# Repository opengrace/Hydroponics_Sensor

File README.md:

Hydroponics_Sensor
==================

**Warning** _currently untested, may contain errors._

An ebb and flow hydroponics or CHPIS aquaponics sensor breakout and controller that uses a NRF24L01 module for communication to other nodes or a central server.

|![image1]|![image2]|
|---|---|
|Board partially populated.||

[image1]: pic-1.JPG "Arduino nano and 10 pin NRF24L01 module"
[image2]: pic-2.JPG "Arduino nano and 10 pin NRF24L01 module"

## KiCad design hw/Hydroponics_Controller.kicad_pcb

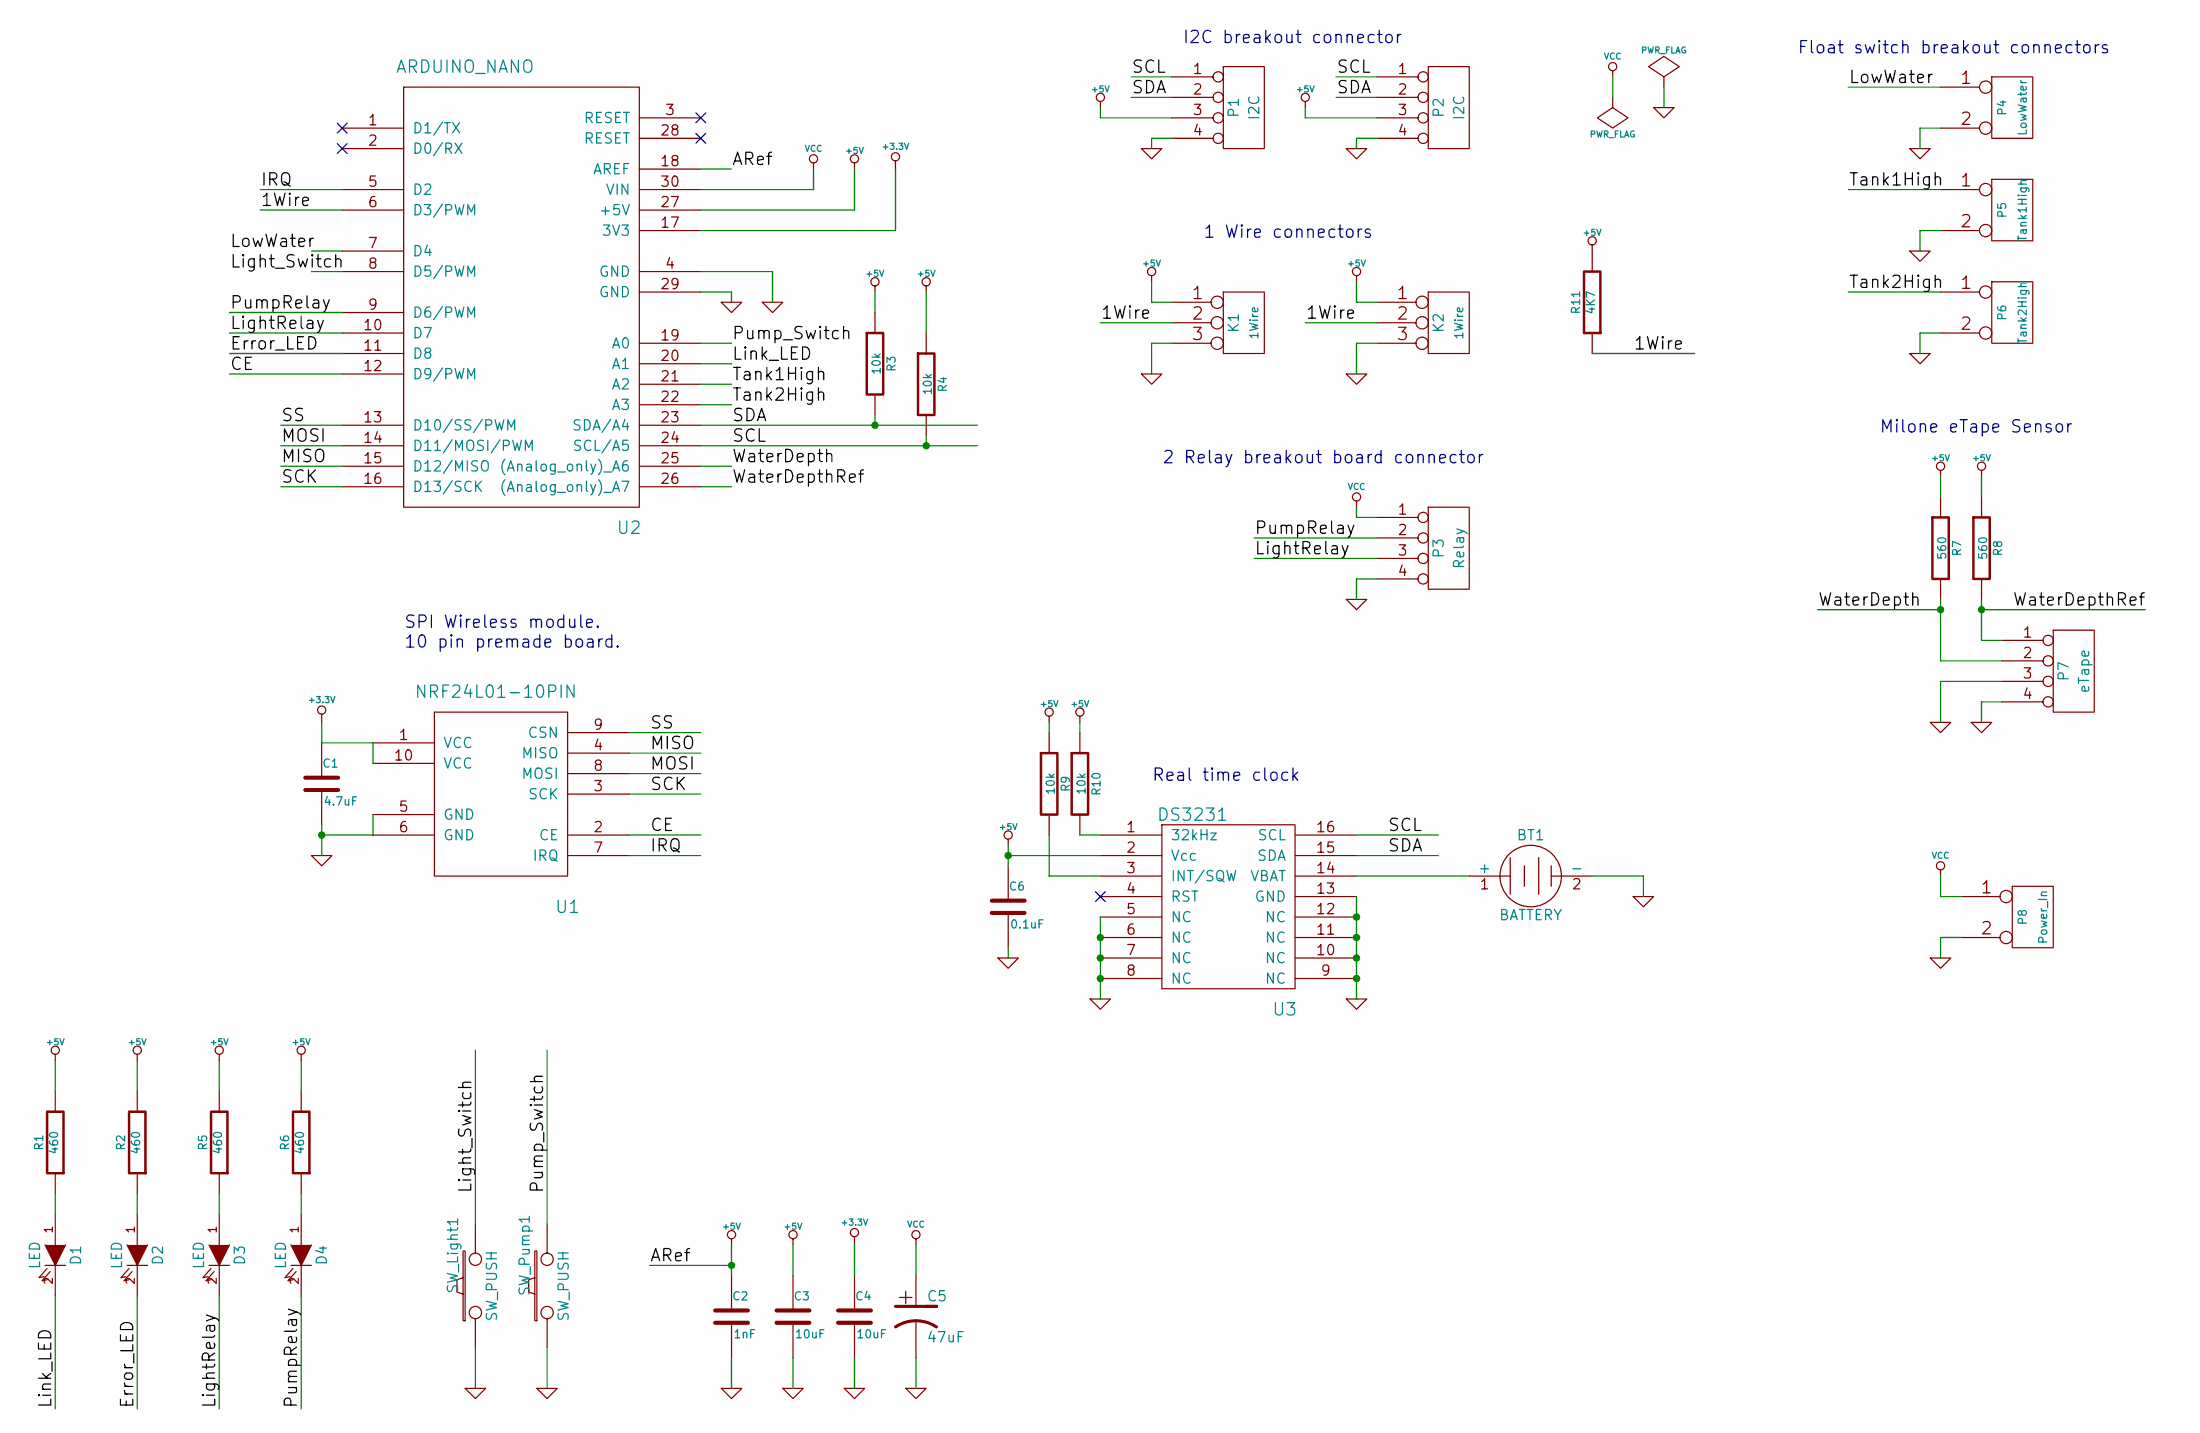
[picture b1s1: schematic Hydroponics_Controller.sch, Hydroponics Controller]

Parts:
BT1: BATTERY
C1: 4.7uF
C2: 1nF
C3, C4: 10uF
C5: 47uF
C6: 0.1uF
D1, D2, D3, D4: LED
K1, K2: 1Wire
P1, P2: I2C
P3: Relay
P4: LowWater
P5: Tank1High
P6: Tank2High
P7: eTape
P8: Power_In
R1, R2, R5, R6: 460
R3, R4, R9, R10: 10k
R7, R8: 560
R11: 4K7
SW_Light1: SW_PUSH
SW_Pump1: SW_PUSH
U1: NRF24L01-10PIN
U2: ARDUINO_NANO
U3: DS3231

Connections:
+3.3V: C1.1, C4.1, U1.1 (VCC), U1.10 (VCC), U2.17 (3V3)
+5V: C2.1, C3.1, C6.1, K1.1, K2.1, P1.3, P2.3, R1.2, R2.2, R3.1, R4.1, R5.2, R6.2, R7.1, R8.1, R9.1, R10.1, R11.2, U2.18 (AREF), U2.27 (+5V), U3.2 (Vcc)
/1Wire: K1.2 (PM), K2.2 (PM), R11.1, U2.6 (D3/PWM)
/CE: U1.2 (CE), U2.12 (D9/PWM)
/Error_LED: D2.2 (K), U2.11 (D8)
/IRQ: U1.7 (IRQ), U2.5 (D2)
/LightRelay: D3.2 (K), P3.3, U2.10 (D7)
/Light_Switch: SW_Light1.2
/Link_LED: D1.2 (K), U2.20 (A1)
/LowWater: P4.1
/MISO: U1.4 (MISO), U2.15 (D12/MISO)
/MOSI: U1.8 (MOSI), U2.14 (D11/MOSI/PWM)
/PumpRelay: D4.2 (K), P3.2, U2.9 (D6/PWM)
/Pump_Switch: SW_Pump1.2, U2.19 (A0)
/SCK: U1.3 (SCK), U2.16 (D13/SCK)
/SCL: P1.1, P2.1, R4.2, U2.24 (SCL/A5), U3.16 (SCL)
/SDA: P1.2, P2.2, R3.2, U2.23 (SDA/A4), U3.15 (SDA)
/SS: U1.9 (CSN), U2.13 (D10/SS/PWM)
/Tank1High: P5.1, U2.21 (A2)
/Tank2High: P6.1, U2.22 (A3)
/WaterDepth: P7.2, R7.2, U2.25 ((Analog_only)_A6)
/WaterDepthRef: P7.1, R8.2, U2.26 ((Analog_only)_A7)
GND: BT1.2 (-), C1.2, C2.2, C3.2, C4.2, C5.2, C6.2, K1.3, K2.3, P1.4, P2.4, P3.4, P4.2 (PM), P5.2 (PM), P6.2 (PM), P7.3, P7.4, P8.2 (PM), SW_Light1.1, SW_Pump1.1, U1.5 (GND), U1.6 (GND), U2.4 (GND), U2.29 (GND), U3.5 (NC), U3.6 (NC), U3.7 (NC), U3.8 (NC), U3.9 (NC), U3.10 (NC), U3.11 (NC), U3.12 (NC), U3.13 (GND)
unnamed: BT1.1 (+), U3.14 (VBAT)
unnamed: D1.1 (A), R1.1
unnamed: D2.1 (A), R2.1
unnamed: D3.1 (A), R5.1
unnamed: D4.1 (A), R6.1
unnamed: R9.2, U3.3 (INT/SQW)
unnamed: R10.2, U3.1 (32kHz)
VCC: C5.1, P3.1, P8.1, U2.30 (VIN)

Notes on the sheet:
SPI Wireless module. 10 pin premade board.
Float switch breakout connectors
Milone eTape Sensor
I2C breakout connector
1 Wire connectors
2 Relay breakout board connector
Real time clock

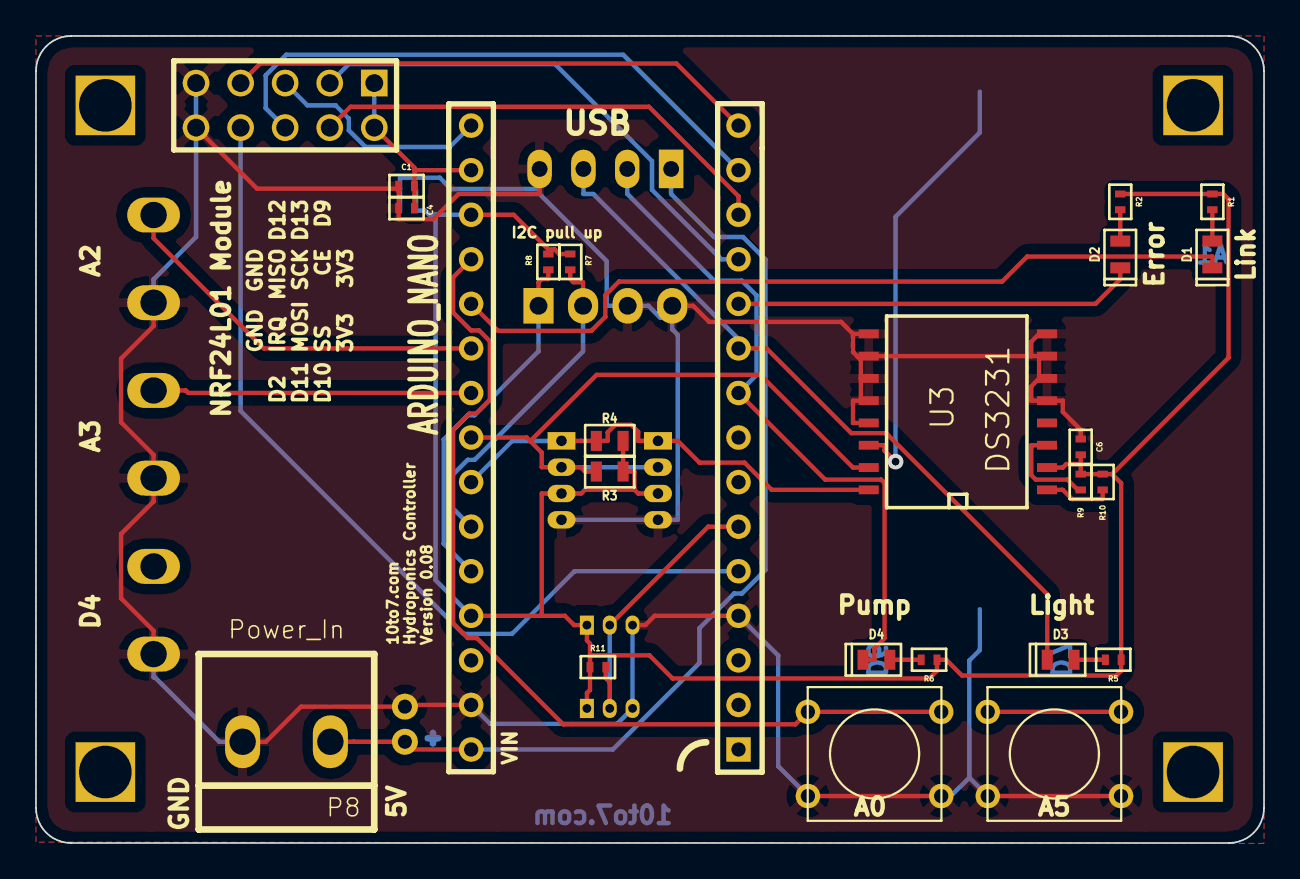
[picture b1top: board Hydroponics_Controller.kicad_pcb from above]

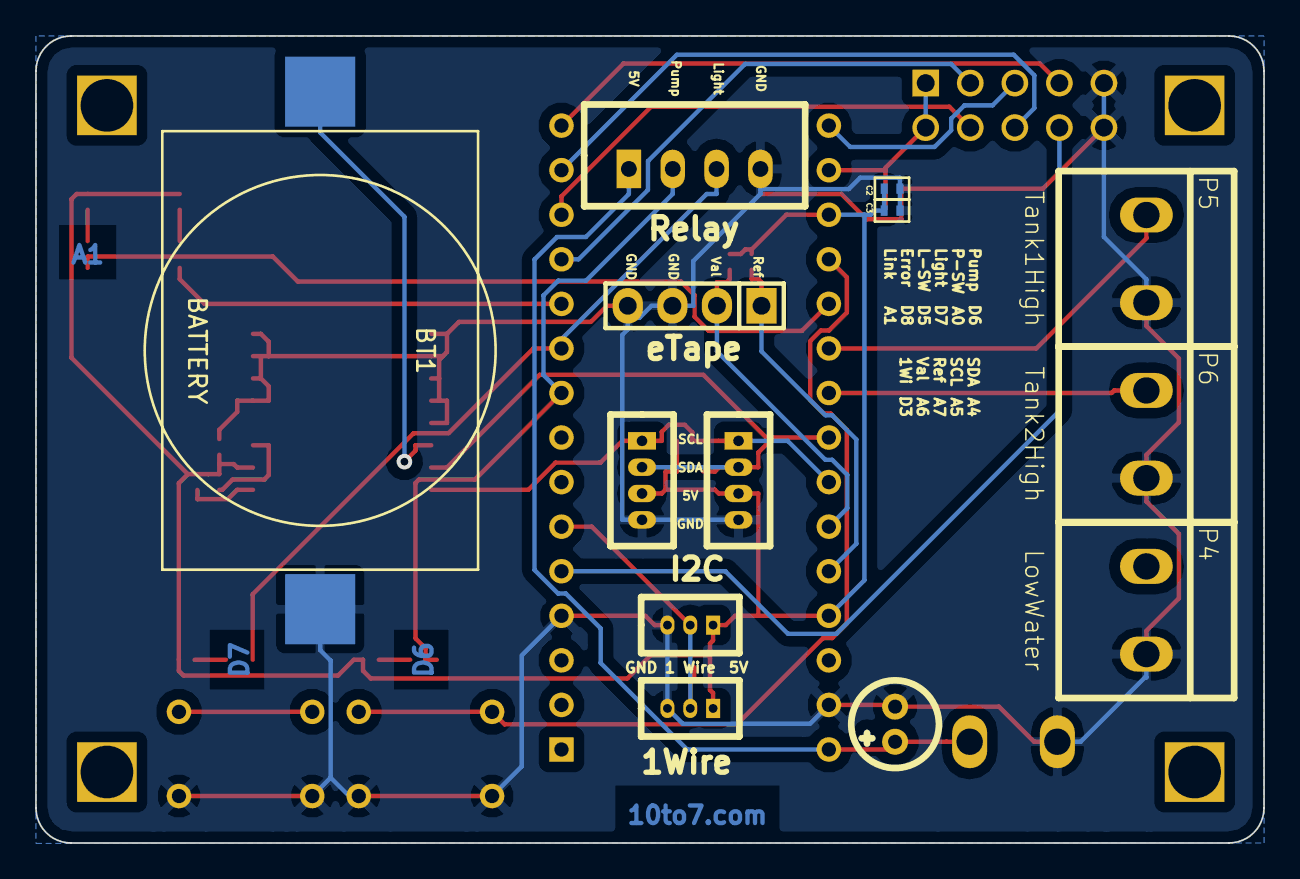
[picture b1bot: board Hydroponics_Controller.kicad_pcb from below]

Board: 2 copper layers, 70.0 x 46.0 mm, 41 parts (13 on the bottom side), 29 nets.

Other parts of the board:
3mmHole_1, 3mmHole_2, 3mmHole_3, 3mmHole_4: VAL**; 3mmHole

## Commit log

2014-05-18 Recreated and moved to new repository
2014-05-31 removed some un-needed components, updated faulty modules and reduced board size.
2014-05-31 and the gerber files
2014-06-01 Fixed text consistency issue in the silkscreen.
2014-06-04 revision 0.03 - update due to the error in the arduino nano footprint
2014-06-26 Added some images of a partially created board.
2014-06-30 Added 3mm mount holes and moved the pull-up resistor. Corrected inconsistency with the netlist and the schematic
2014-06-30 moved the pcb silkscreen of the etape
2014-06-30 another silkscreen error fixed
2014-07-02 Added PCB images
2014-07-02 Something wierd is happening with Kicad. GND nets were appearing as VCC in PCB new.
2014-07-05 remade the board. Something went wrong with ki-cad and the mask wasn't fitting correctly.
2014-07-05 fixed small error on the silk screen
2014-07-27 Added RTC to board. Corrected error using A6/A7 as digital pins...
2014-07-28 Some basic functionality added - pump cycle, low water and date from wireless.
2014-07-28 logic fail in the setup call to the alarms. alarm.Delay also missing.
2014-07-29 Alarms doesn't seem to play nice with another library, removed it and added simple logic which should give similar results
2014-07-30 Updated the PCB render
2014-08-01 overrun was being over zealous and prevented all pump activity after the maxPumpRun time following a reset.
2014-08-03 Fixed the missing pullup resistor from the 1 wire connector
2014-09-13 Script updated to reflect the pin changes in version 0.7. Note still in development.
2014-09-27 Enabled the light button
    actually made the light button functional.
2014-09-27 removed sillyness.
2014-10-10 updated to fix I2C connected to wrong pins. Also changed cap to 0402
2014-11-07 Added pdf of the schematic
